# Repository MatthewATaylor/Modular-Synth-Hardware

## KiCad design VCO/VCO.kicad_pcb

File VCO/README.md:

# VCO

A simple voltage controlled oscillator based on the [VCO-1 design by Thomas Henry](https://www.birthofasynth.com/Thomas_Henry/Pages/VCO-1.html), including:

* Triangle, sine, PWM, and sawtooth outputs
* Linear and exponential FM
* A switch for choosing between slow (LFO) and fast (1V/oct, audio rate) frequency ranges

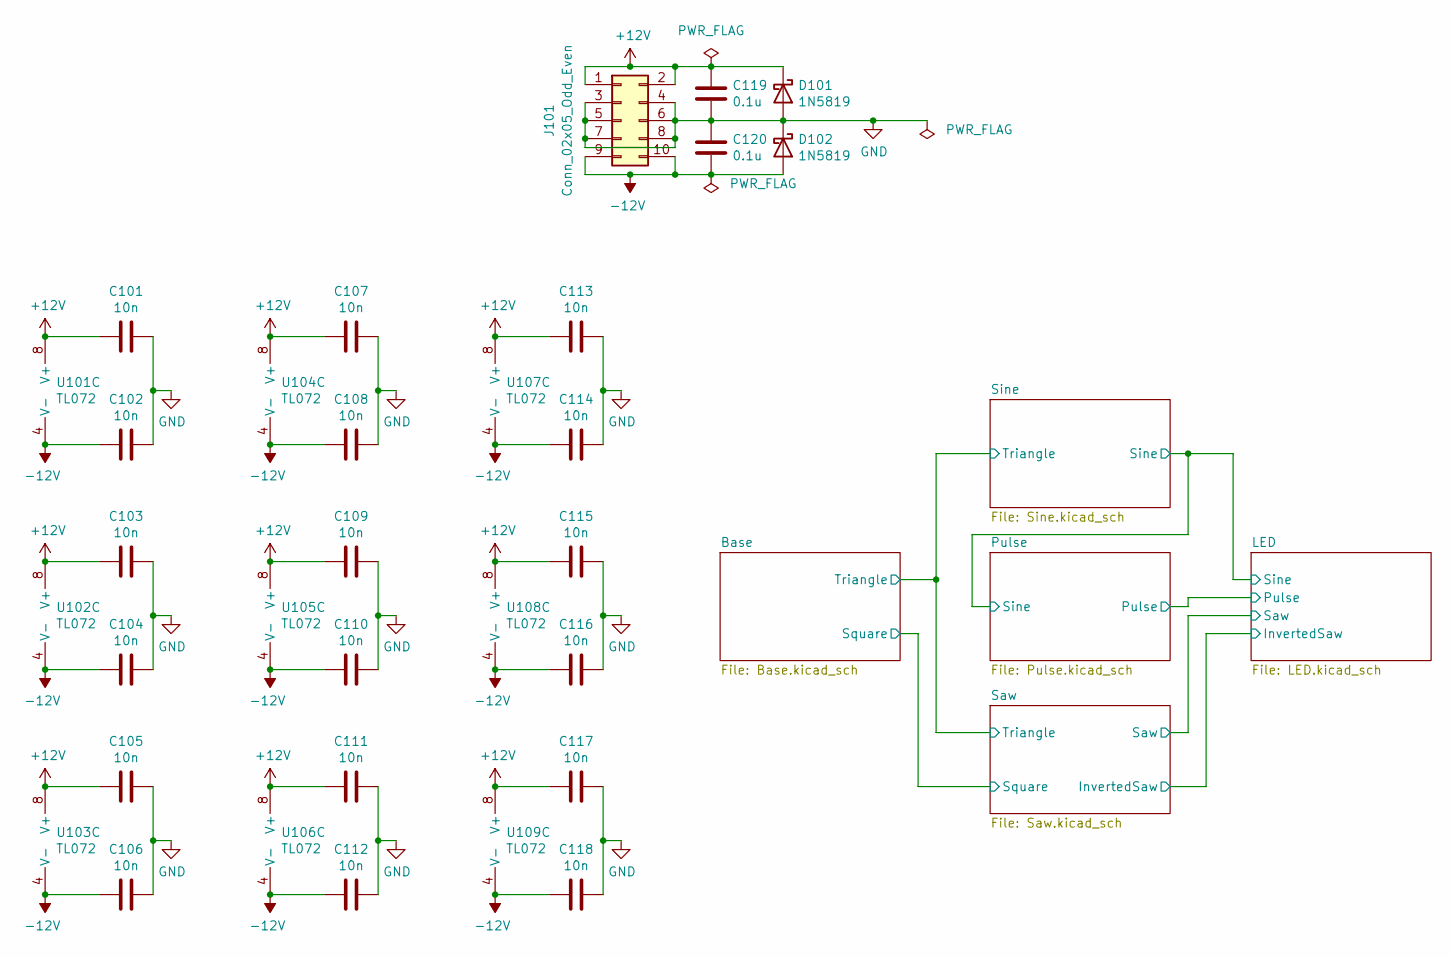
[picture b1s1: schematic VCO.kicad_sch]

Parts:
C101, C102, C103, C104, C105, C106, C107, C108, C109, C110, C111, C112, C113, C114, C115, C116, C117, C118: 10n; C_Disc_D5.0mm_W2.5mm_P5.00mm
C119, C120: 0.1u; C_Disc_D5.0mm_W2.5mm_P5.00mm
D101, D102: 1N5819; D_DO-41_SOD81_P10.16mm_Horizontal
J101: Conn_02x05_Odd_Even; PinHeader_2x05_P2.54mm_Vertical
U101, U102, U103, U104, U105, U106, U107, U108, U109: TL072; DIP-8_W7.62mm_Socket

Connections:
+12V: C101.1, C103.1, C105.1, C107.1, C109.1, C111.1, C113.1, C115.1, C117.1, C119.1, D101.1 (K), J101.1, J101.2, U101.8 (V+), U102.8 (V+), U103.8 (V+), U104.8 (V+), U105.8 (V+), U106.8 (V+), U107.8 (V+), U108.8 (V+), U109.8 (V+); also elsewhere on the board
-12V: C102.1, C104.1, C106.1, C108.1, C110.1, C112.1, C114.1, C116.1, C118.1, C120.2, D102.2 (A), J101.9, J101.10, U101.4 (V-), U102.4 (V-), U103.4 (V-), U104.4 (V-), U105.4 (V-), U106.4 (V-), U107.4 (V-), U108.4 (V-), U109.4 (V-); also elsewhere on the board
GND: C101.2, C102.2, C103.2, C104.2, C105.2, C106.2, C107.2, C108.2, C109.2, C110.2, C111.2, C112.2, C113.2, C114.2, C115.2, C116.2, C117.2, C118.2, C119.2, C120.1, D101.2 (A), D102.1 (K), J101.3, J101.4, J101.5, J101.6, J101.7, J101.8; also elsewhere on the board

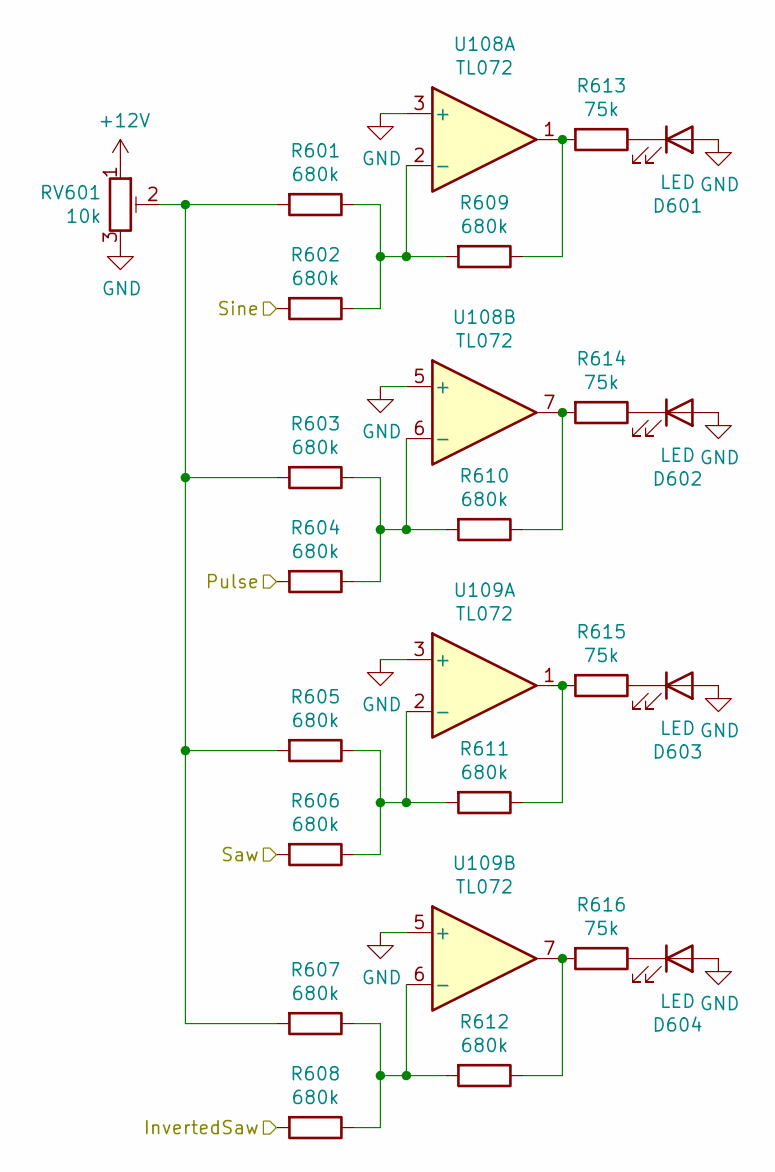
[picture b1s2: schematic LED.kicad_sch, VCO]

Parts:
D601, D602, D603, D604: LED; LED_D5.0mm
R601, R602, R603, R604, R605, R606, R607, R608, R609, R610, R611, R612: 680k; R_Axial_DIN0207_L6.3mm_D2.5mm_P7.62mm_Horizontal
R613, R614, R615, R616: 75k; R_Axial_DIN0207_L6.3mm_D2.5mm_P7.62mm_Horizontal
RV601: 10k; Potentiometer_Runtron_RM-065_Vertical_Improved
U108, U109: TL072; DIP-8_W7.62mm_Socket

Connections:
+12V: RV601.1; also elsewhere on the board
/LED/InvertedSaw: R608.2; also elsewhere on the board
/LED/Pulse: R604.2; also elsewhere on the board
/LED/Saw: R606.2; also elsewhere on the board
/LED/Sine: R602.2; also elsewhere on the board
GND: D601.2 (A), D602.2 (A), D603.2 (A), D604.2 (A), RV601.3, U108.3 (+), U108.5 (+), U109.3 (+), U109.5 (+); also elsewhere on the board
unnamed: D601.1 (K), R613.1
unnamed: D602.1 (K), R614.1
unnamed: D603.1 (K), R615.1
unnamed: D604.1 (K), R616.1
unnamed: R601.1, R602.1, R609.2, U108.2 (-)
unnamed: R601.2, R603.2, R605.2, R607.2, RV601.2
unnamed: R603.1, R604.1, R610.2, U108.6 (-)
unnamed: R605.1, R606.1, R611.2, U109.2 (-)
unnamed: R607.1, R608.1, R612.2, U109.6 (-)
unnamed: R609.1, R613.2, U108.1
unnamed: R610.1, R614.2, U108.7
unnamed: R611.1, R615.2, U109.1
unnamed: R612.1, R616.2, U109.7

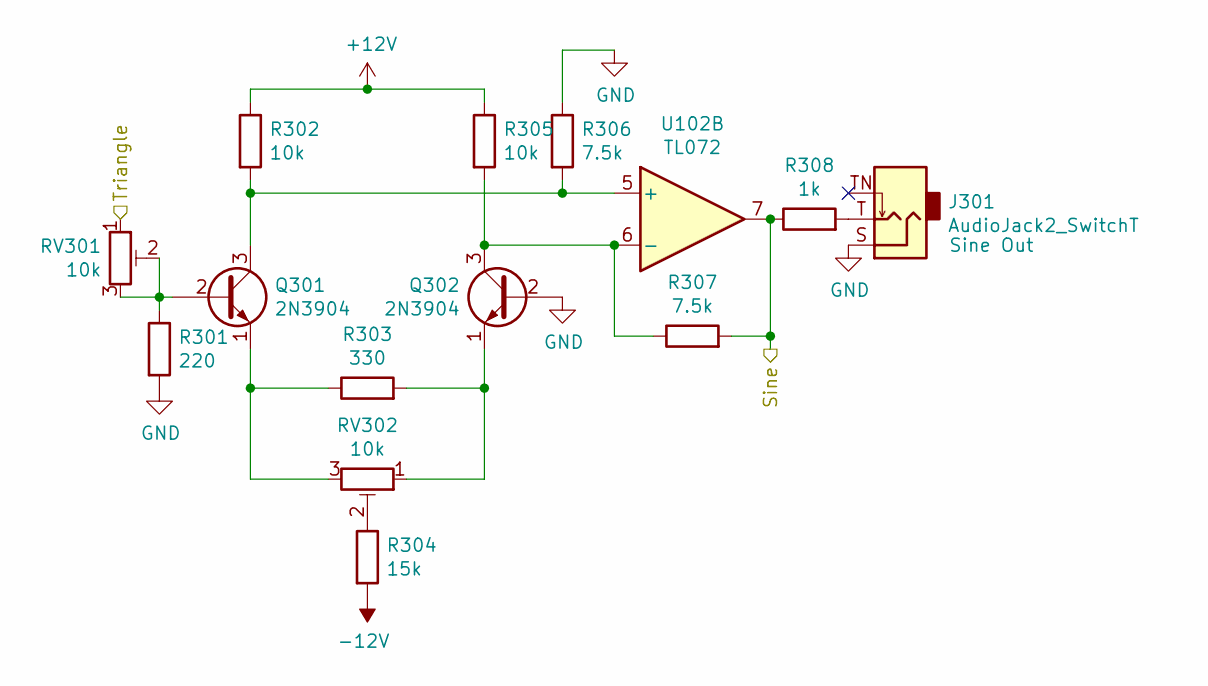
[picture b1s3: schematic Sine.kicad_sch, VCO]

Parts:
J301: AudioJack2_SwitchT; Jack_3.5mm_QingPu_WQP-PJ398SM_Vertical_CircularHoles
Q301, Q302: 2N3904; TO-92_Inline
R301: 220; R_Axial_DIN0207_L6.3mm_D2.5mm_P7.62mm_Horizontal
R302, R305: 10k; R_Axial_DIN0207_L6.3mm_D2.5mm_P7.62mm_Horizontal
R303: 330; R_Axial_DIN0207_L6.3mm_D2.5mm_P7.62mm_Horizontal
R304: 15k; R_Axial_DIN0207_L6.3mm_D2.5mm_P7.62mm_Horizontal
R306, R307: 7.5k; R_Axial_DIN0207_L6.3mm_D2.5mm_P7.62mm_Horizontal
R308: 1k; R_Axial_DIN0207_L6.3mm_D2.5mm_P7.62mm_Horizontal
RV301, RV302: 10k; Potentiometer_Runtron_RM-065_Vertical_Improved
U102: TL072; DIP-8_W7.62mm_Socket

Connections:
+12V: R302.1, R305.1; also elsewhere on the board
-12V: R304.2; also elsewhere on the board
/Base/Triangle: RV301.1; also elsewhere on the board
/LED/Sine: R307.2, R308.1, U102.7; also elsewhere on the board
GND: J301.S, Q302.2 (B), R301.2, R306.1; also elsewhere on the board
unnamed: J301.T, R308.2
unnamed: Q301.1 (E), R303.1, RV302.3
unnamed: Q301.2 (B), R301.1, RV301.2, RV301.3
unnamed: Q301.3 (C), R302.2, R306.2, U102.5 (+)
unnamed: Q302.1 (E), R303.2, RV302.1
unnamed: Q302.3 (C), R305.2, R307.1, U102.6 (-)
unnamed: R304.1, RV302.2

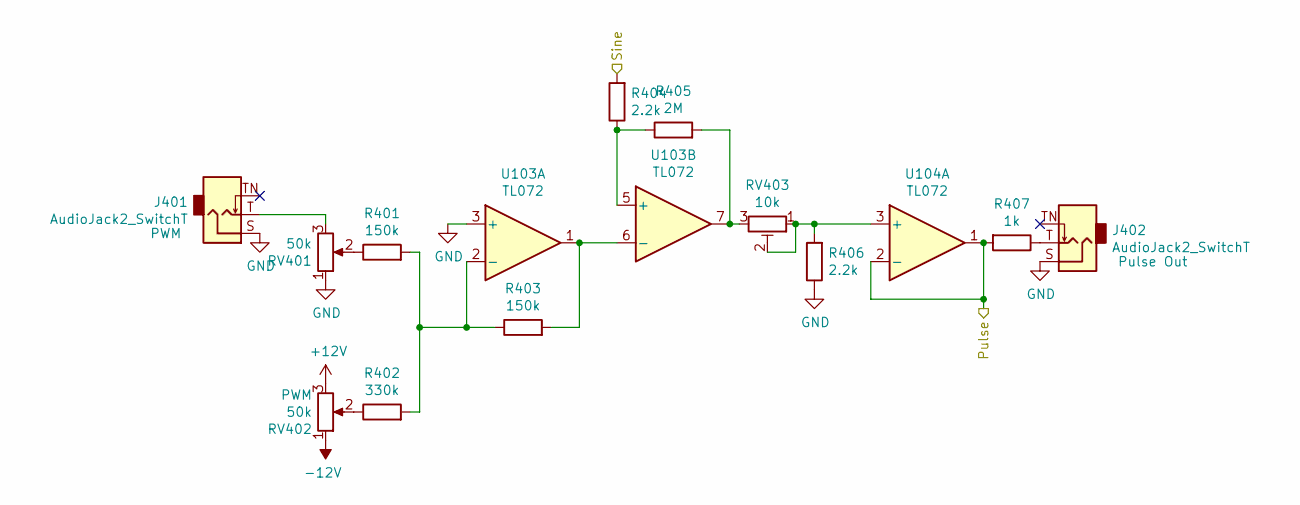
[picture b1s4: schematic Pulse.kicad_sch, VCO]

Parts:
J401, J402: AudioJack2_SwitchT; Jack_3.5mm_QingPu_WQP-PJ398SM_Vertical_CircularHoles
R401, R403: 150k; R_Axial_DIN0207_L6.3mm_D2.5mm_P7.62mm_Horizontal
R402: 330k; R_Axial_DIN0207_L6.3mm_D2.5mm_P7.62mm_Horizontal
R404, R406: 2.2k; R_Axial_DIN0207_L6.3mm_D2.5mm_P7.62mm_Horizontal
R405: 2M; R_Axial_DIN0207_L6.3mm_D2.5mm_P7.62mm_Horizontal
R407: 1k; R_Axial_DIN0207_L6.3mm_D2.5mm_P7.62mm_Horizontal
RV401, RV402: 50k; Potentiometer_Alpha_RD901F-40-00D_Single_Vertical_CircularH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
RV403: 10k; Potentiometer_Runtron_RM-065_Vertical_Improved
U103, U104: TL072; DIP-8_W7.62mm_Socket

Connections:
+12V: RV402.3; also elsewhere on the board
-12V: RV402.1; also elsewhere on the board
/LED/Pulse: R407.2, U104.1, U104.2 (-); also elsewhere on the board
/LED/Sine: R404.2; also elsewhere on the board
GND: J401.S, J402.S, R406.1, RV401.1, U103.3 (+); also elsewhere on the board
unnamed: J401.T, RV401.3
unnamed: J402.T, R407.1
unnamed: R401.1, RV401.2
unnamed: R401.2, R402.2, R403.1, U103.2 (-)
unnamed: R402.1, RV402.2
unnamed: R403.2, U103.1, U103.6 (-)
unnamed: R404.1, R405.1, U103.5 (+)
unnamed: R405.2, RV403.3, U103.7
unnamed: R406.2, RV403.1, RV403.2, U104.3 (+)

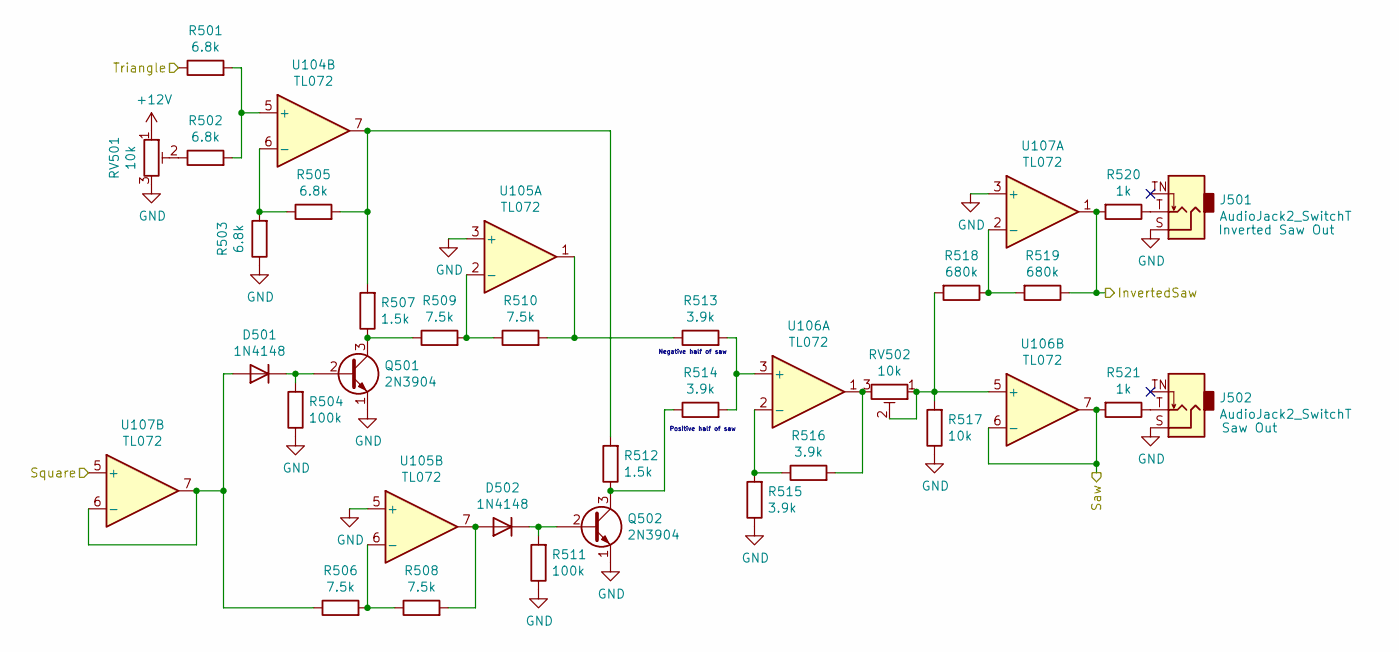
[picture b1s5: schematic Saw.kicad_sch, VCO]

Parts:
D501, D502: 1N4148; D_DO-35_SOD27_P7.62mm_Horizontal
J501, J502: AudioJack2_SwitchT; Jack_3.5mm_QingPu_WQP-PJ398SM_Vertical_CircularHoles
Q501, Q502: 2N3904; TO-92_Inline
R501, R502, R503, R505: 6.8k; R_Axial_DIN0207_L6.3mm_D2.5mm_P7.62mm_Horizontal
R504, R511: 100k; R_Axial_DIN0207_L6.3mm_D2.5mm_P7.62mm_Horizontal
R506, R508, R509, R510: 7.5k; R_Axial_DIN0207_L6.3mm_D2.5mm_P7.62mm_Horizontal
R507, R512: 1.5k; R_Axial_DIN0207_L6.3mm_D2.5mm_P7.62mm_Horizontal
R513, R514, R515, R516: 3.9k; R_Axial_DIN0207_L6.3mm_D2.5mm_P7.62mm_Horizontal
R517: 10k; R_Axial_DIN0207_L6.3mm_D2.5mm_P7.62mm_Horizontal
R518, R519: 680k; R_Axial_DIN0207_L6.3mm_D2.5mm_P7.62mm_Horizontal
R520, R521: 1k; R_Axial_DIN0207_L6.3mm_D2.5mm_P7.62mm_Horizontal
RV501, RV502: 10k; Potentiometer_Runtron_RM-065_Vertical_Improved
U104, U105, U106, U107: TL072; DIP-8_W7.62mm_Socket

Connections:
+12V: RV501.1; also elsewhere on the board
/Base/Square: U107.5 (+); also elsewhere on the board
/Base/Triangle: R501.1; also elsewhere on the board
/LED/InvertedSaw: R519.1, R520.2, U107.1; also elsewhere on the board
/LED/Saw: R521.2, U106.6 (-), U106.7; also elsewhere on the board
GND: J501.S, J502.S, Q501.1 (E), Q502.1 (E), R503.1, R504.1, R511.1, R515.1, R517.1, RV501.3, U105.3 (+), U105.5 (+), U107.3 (+); also elsewhere on the board
unnamed: D501.1 (K), Q501.2 (B), R504.2
unnamed: D501.2 (A), R506.1, U107.6 (-), U107.7
unnamed: D502.1 (K), Q502.2 (B), R511.2
unnamed: D502.2 (A), R508.2, U105.7
unnamed: J501.T, R520.1
unnamed: J502.T, R521.1
unnamed: Q501.3 (C), R507.1, R509.1
unnamed: Q502.3 (C), R512.1, R514.1
unnamed: R501.2, R502.2, U104.5 (+)
unnamed: R502.1, RV501.2
unnamed: R503.2, R505.1, U104.6 (-)
unnamed: R505.2, R507.2, R512.2, U104.7
unnamed: R506.2, R508.1, U105.6 (-)
unnamed: R509.2, R510.1, U105.2 (-)
unnamed: R510.2, R513.1, U105.1
unnamed: R513.2, R514.2, U106.3 (+)
unnamed: R515.2, R516.1, U106.2 (-)
unnamed: R516.2, RV502.3, U106.1
unnamed: R517.2, R518.2, RV502.1, RV502.2, U106.5 (+)
unnamed: R518.1, R519.2, U107.2 (-)

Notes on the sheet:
Positive half of saw
Negative half of saw

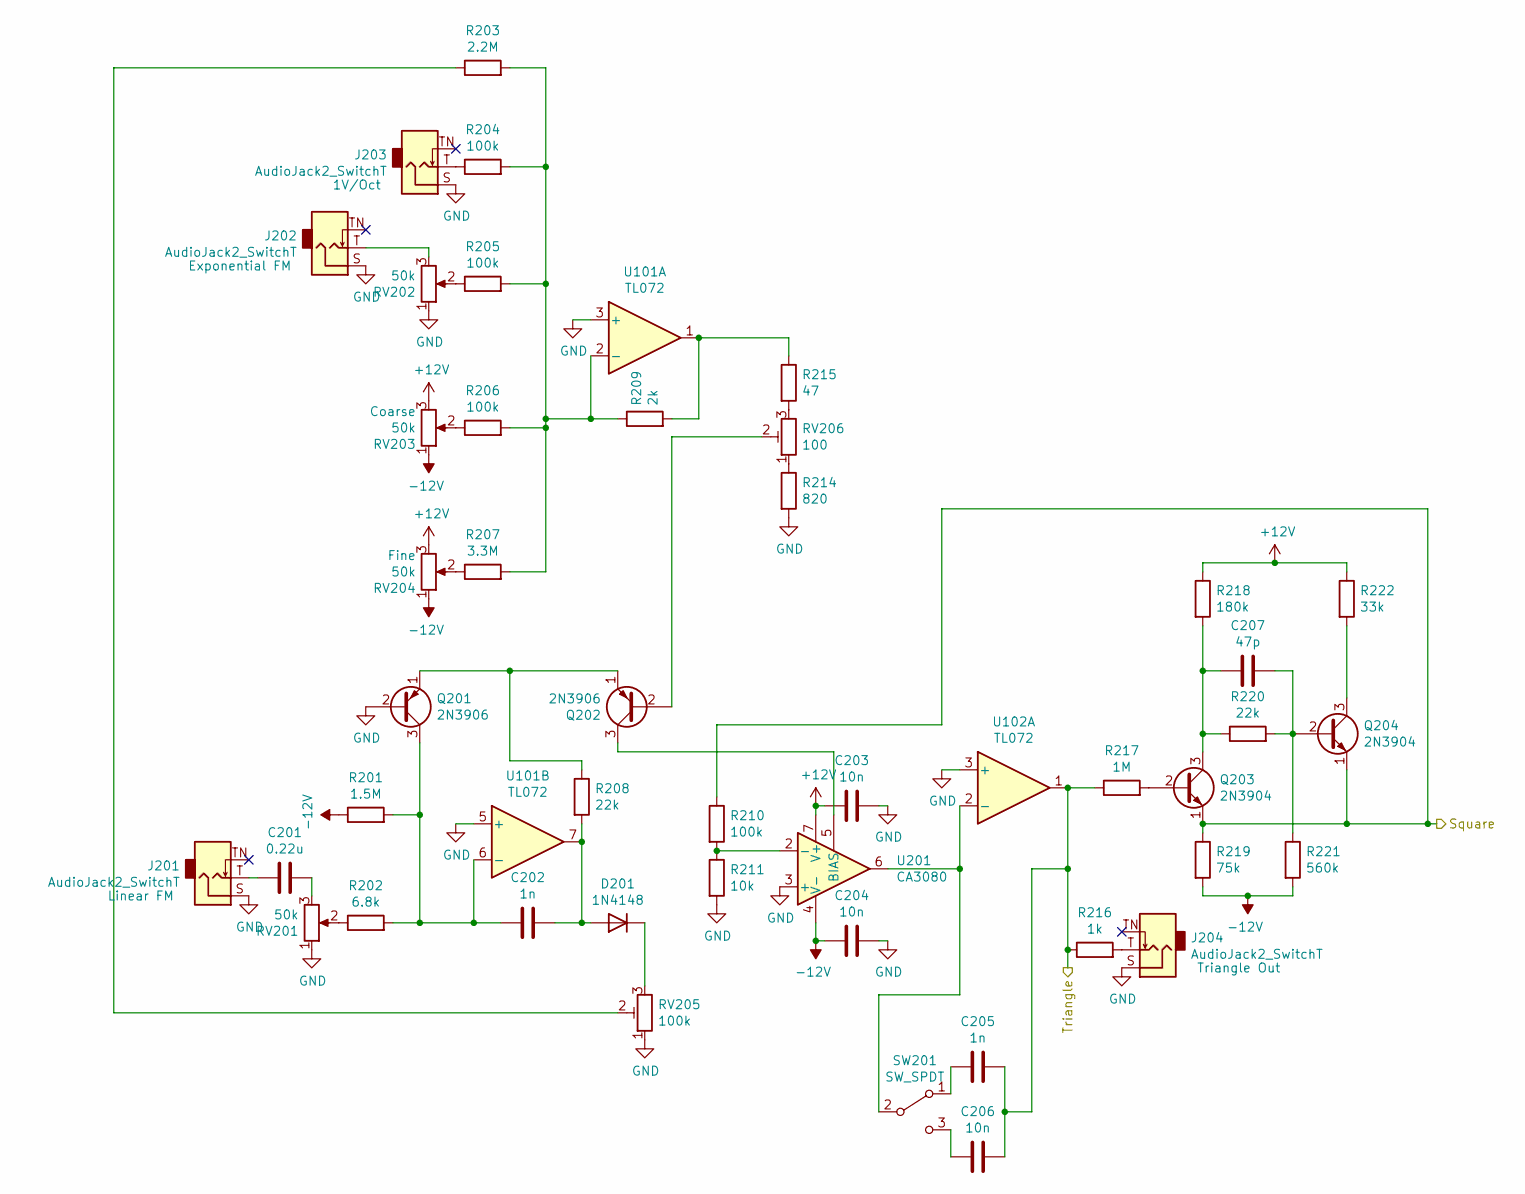
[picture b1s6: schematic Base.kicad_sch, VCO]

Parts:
C201: 0.22u; C_Disc_D5.0mm_W2.5mm_P5.00mm
C202, C205: 1n; C_Disc_D5.0mm_W2.5mm_P5.00mm
C203, C204, C206: 10n; C_Disc_D5.0mm_W2.5mm_P5.00mm
C207: 47p; C_Disc_D5.0mm_W2.5mm_P5.00mm
D201: 1N4148; D_DO-35_SOD27_P7.62mm_Horizontal
J201, J202, J203, J204: AudioJack2_SwitchT; Jack_3.5mm_QingPu_WQP-PJ398SM_Vertical_CircularHoles
Q201, Q202: 2N3906; TO-92_Inline
Q203, Q204: 2N3904; TO-92_Inline
R201: 1.5M; R_Axial_DIN0207_L6.3mm_D2.5mm_P7.62mm_Horizontal
R202: 6.8k; R_Axial_DIN0207_L6.3mm_D2.5mm_P7.62mm_Horizontal
R203: 2.2M; R_Axial_DIN0207_L6.3mm_D2.5mm_P7.62mm_Horizontal
R204, R205, R206, R210: 100k; R_Axial_DIN0207_L6.3mm_D2.5mm_P7.62mm_Horizontal
R207: 3.3M; R_Axial_DIN0207_L6.3mm_D2.5mm_P7.62mm_Horizontal
R208, R220: 22k; R_Axial_DIN0207_L6.3mm_D2.5mm_P7.62mm_Horizontal
R209: 2k; R_Axial_DIN0207_L6.3mm_D2.5mm_P7.62mm_Horizontal
R211: 10k; R_Axial_DIN0207_L6.3mm_D2.5mm_P7.62mm_Horizontal
R214: 820; R_Axial_DIN0207_L6.3mm_D2.5mm_P7.62mm_Horizontal
R215: 47; R_Axial_DIN0207_L6.3mm_D2.5mm_P7.62mm_Horizontal
R216: 1k; R_Axial_DIN0207_L6.3mm_D2.5mm_P7.62mm_Horizontal
R217: 1M; R_Axial_DIN0207_L6.3mm_D2.5mm_P7.62mm_Horizontal
R218: 180k; R_Axial_DIN0207_L6.3mm_D2.5mm_P7.62mm_Horizontal
R219: 75k; R_Axial_DIN0207_L6.3mm_D2.5mm_P7.62mm_Horizontal
R221: 560k; R_Axial_DIN0207_L6.3mm_D2.5mm_P7.62mm_Horizontal
R222: 33k; R_Axial_DIN0207_L6.3mm_D2.5mm_P7.62mm_Horizontal
RV201, RV202, RV203, RV204: 50k; Potentiometer_Alpha_RD901F-40-00D_Single_Vertical_CircularH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
RV205: 100k; Potentiometer_Bourns_3296W_Vertical
RV206: 100; Potentiometer_Bourns_3296W_Vertical
SW201: SW_SPDT; MTS-102_MTS-103_MTS-112_MTS-113_MTS-123
U101, U102: TL072; DIP-8_W7.62mm_Socket
U201: CA3080; DIP-8_W7.62mm_Socket

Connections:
+12V: C203.1, R218.1, R222.1, RV203.3, RV204.3, U201.7 (V+); also elsewhere on the board
-12V: C204.1, R201.1, R219.2, R221.2, RV203.1, RV204.1, U201.4 (V-); also elsewhere on the board
/Base/Square: Q203.1 (E), Q204.1 (E), R210.1, R219.1; also elsewhere on the board
/Base/Triangle: C205.2, C206.2, R216.1, R217.1, U102.1; also elsewhere on the board
GND: C203.2, C204.2, J201.S, J202.S, J203.S, J204.S, Q201.2 (B), R211.2, R214.2, RV201.1, RV202.1, RV205.1, U101.3 (+), U101.5 (+), U102.3 (+), U201.3 (+); also elsewhere on the board
unnamed: C201.1, J201.T
unnamed: C201.2, RV201.3
unnamed: C202.1, Q201.3 (C), R201.2, R202.2, U101.6 (-)
unnamed: C202.2, D201.2 (A), R208.2, U101.7
unnamed: C205.1, SW201.1 (A)
unnamed: C206.1, SW201.3 (C)
unnamed: C207.1, Q203.3 (C), R218.2, R220.1
unnamed: C207.2, Q204.2 (B), R220.2, R221.1
unnamed: D201.1 (K), RV205.3
unnamed: J202.T, RV202.3
unnamed: J203.T, R204.1
unnamed: J204.T, R216.2
unnamed: Q201.1 (E), Q202.1 (E), R208.1
unnamed: Q202.2 (B), RV206.2
unnamed: Q202.3 (C), U201.5 (BIAS)
unnamed: Q203.2 (B), R217.2
unnamed: Q204.3 (C), R222.2
unnamed: R202.1, RV201.2
unnamed: R203.1, RV205.2
unnamed: R203.2, R204.2, R205.2, R206.2, R207.2, R209.1, U101.2 (-)
unnamed: R205.1, RV202.2
unnamed: R206.1, RV203.2
unnamed: R207.1, RV204.2
unnamed: R209.2, R215.1, U101.1
unnamed: R210.2, R211.1, U201.2 (-)
unnamed: R214.1, RV206.1
unnamed: R215.2, RV206.3
unnamed: SW201.2 (B), U102.2 (-), U201.6

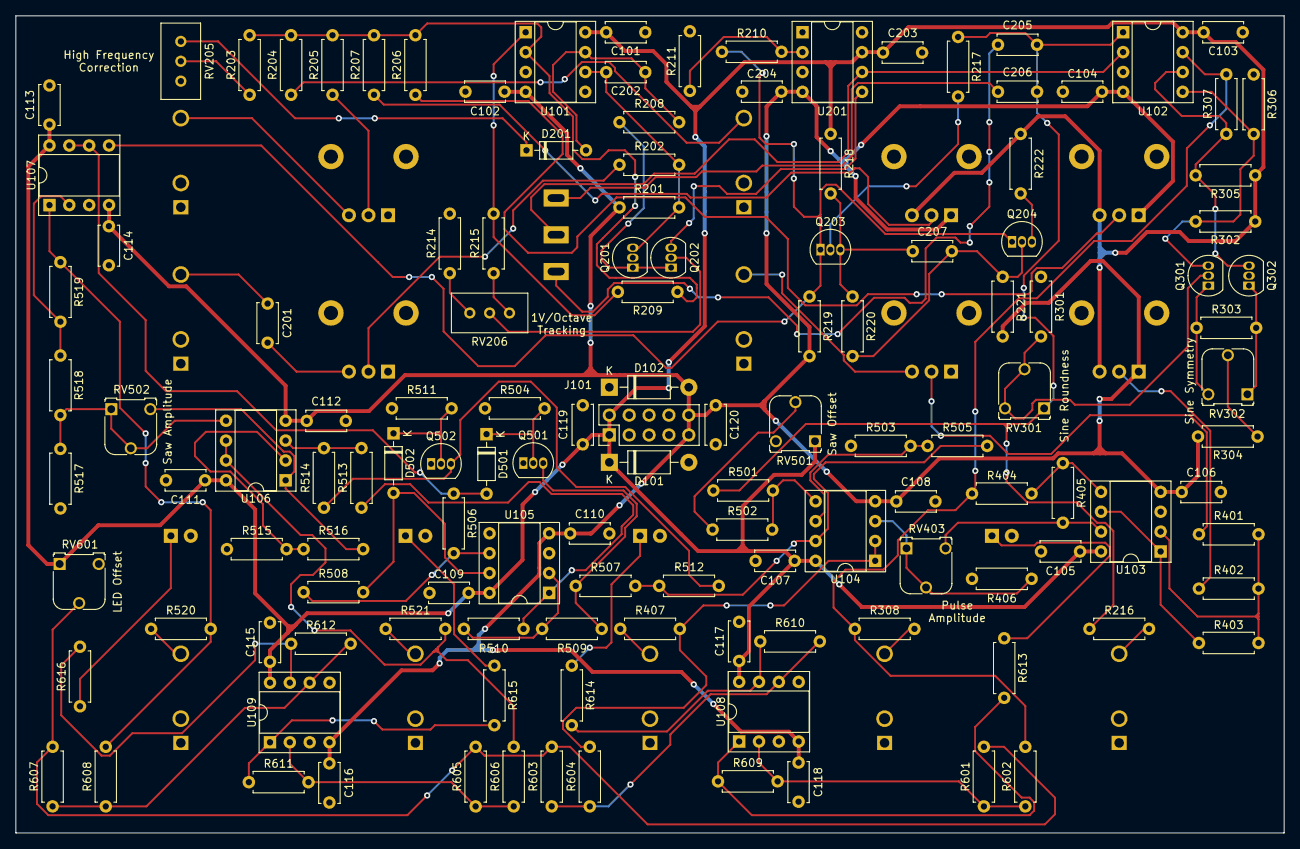
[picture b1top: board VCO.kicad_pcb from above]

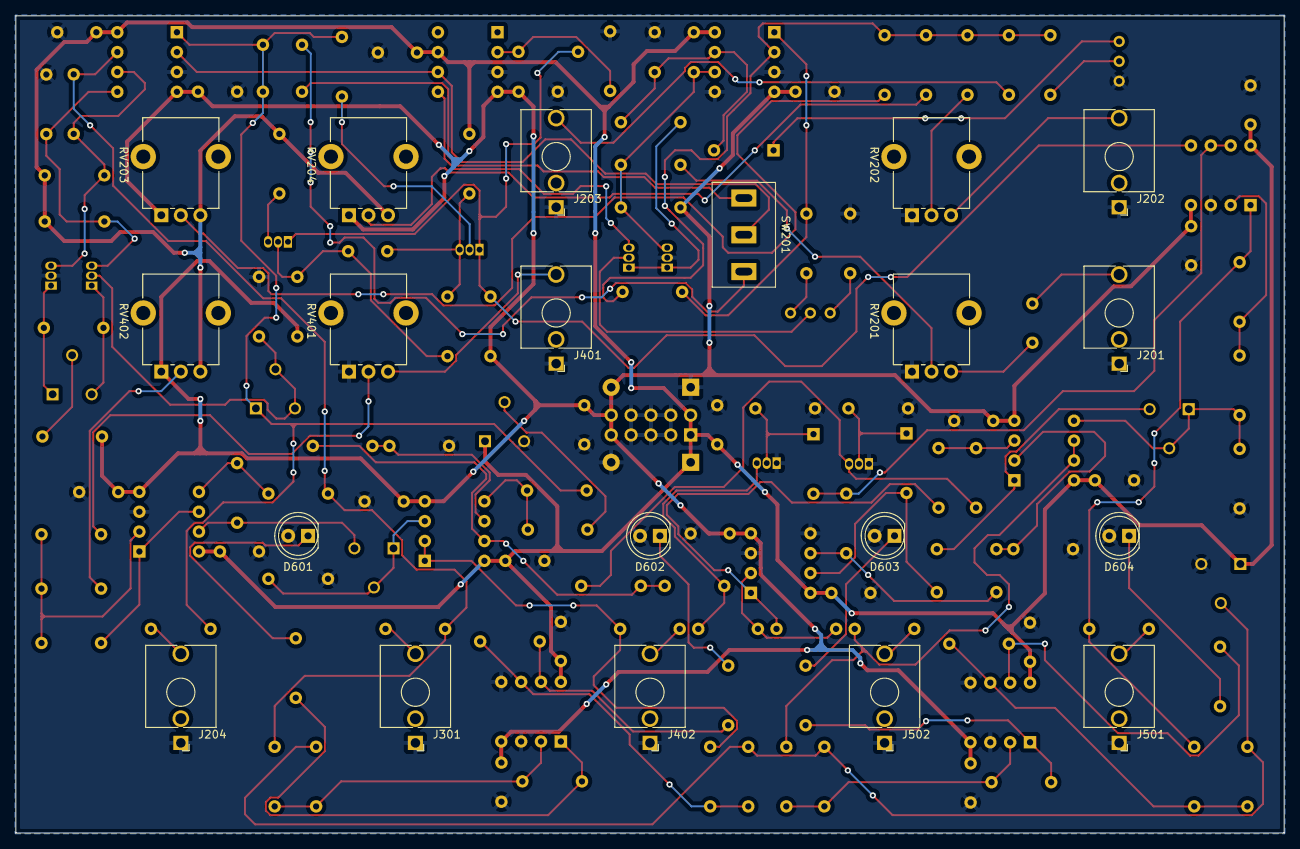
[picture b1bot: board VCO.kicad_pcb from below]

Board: 2 copper layers, 162.2 x 104.5 mm, 151 parts (20 on the bottom side), 86 nets.

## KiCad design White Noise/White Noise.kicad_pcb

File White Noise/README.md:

# White Noise

A white noise generator based on [René Schmitz's design](https://www.schmitzbits.de/noise.html).

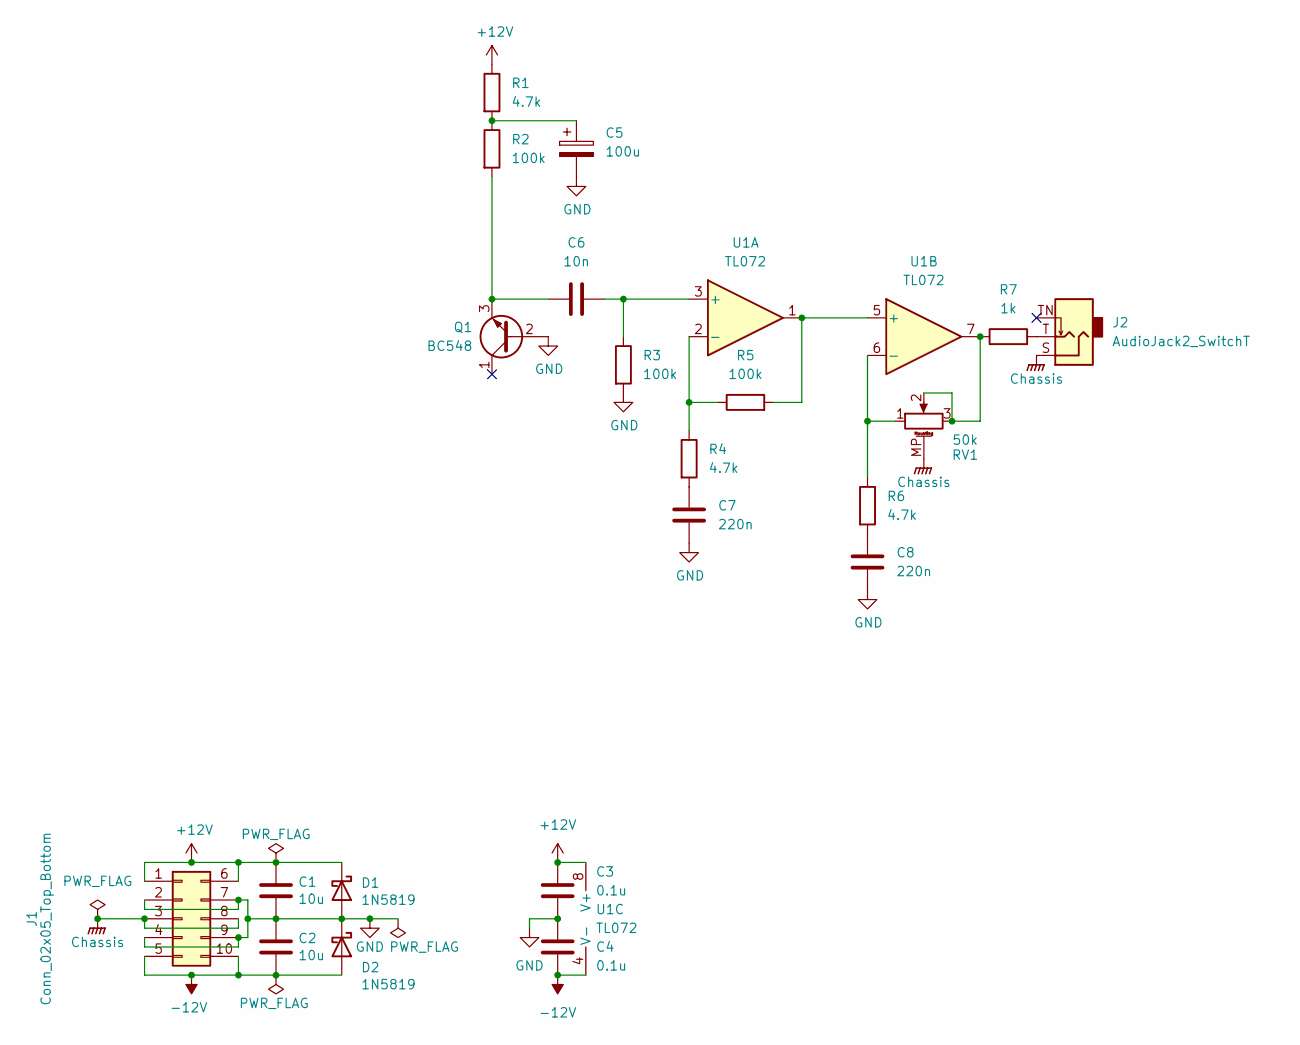
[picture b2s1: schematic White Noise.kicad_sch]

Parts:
C1, C2: 10u; C_Disc_D5.5mm_W4.0mm_P2.50mm
C3, C4: 0.1u; C_Disc_D5.5mm_W2.5mm_P2.50mm
C5: 100u; CP_Radial_D5.0mm_P2.00mm
C6: 10n; C_Disc_D5.5mm_W2.5mm_P2.50mm
C7, C8: 220n; C_Disc_D5.5mm_W2.5mm_P2.50mm
D1, D2: 1N5819; D_DO-41_SOD81_P10.16mm_Horizontal
J1: Conn_02x05_Top_Bottom; Molex_Mini-Fit_Jr_5566-10A_2x05_P4.20mm_Vertical
J2: AudioJack2_SwitchT; Jack_3.5mm_QingPu_WQP-PJ398SM_Vertical_CircularHoles
Q1: BC548; TO-92_HandSolder
R1, R4, R6: 4.7k; R_Axial_DIN0207_L6.3mm_D2.5mm_P7.62mm_Horizontal
R2, R3, R5: 100k; R_Axial_DIN0207_L6.3mm_D2.5mm_P7.62mm_Horizontal
R7: 1k; R_Axial_DIN0207_L6.3mm_D2.5mm_P7.62mm_Horizontal
RV1: 50k; Potentiometer_Alpha_RD901F-40-00D_Single_Vertical_MP
U1: TL072; DIP-8_W7.62mm_Socket

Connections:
+12V: C1.1, C3.2, D1.1 (K), J1.1, J1.6, R1.1, U1.8 (V+)
-12V: C2.2, C4.1, D2.2 (A), J1.5, J1.10, U1.4 (V-)
Chassis: J1.3, J1.8, J2.S, RV1.MP (MountPin)
GND: C1.2, C2.1, C3.1, C4.2, C5.2, C7.1, C8.1, D1.2 (A), D2.1 (K), J1.2, J1.4, J1.7, J1.9, Q1.2 (B), R3.2
unnamed: C5.1, R1.2, R2.1
unnamed: C7.2, R4.2
unnamed: C8.2, R6.2
unnamed: J2.T, R7.2
unnamed: C6.1, Q1.3 (E), R2.2
unnamed: R7.1, RV1.2, RV1.3, U1.7
unnamed: C6.2, R3.1, U1.3 (+)
unnamed: R4.1, R5.1, U1.2 (-)
unnamed: R5.2, U1.1, U1.5 (+)
unnamed: R6.1, RV1.1, U1.6 (-)

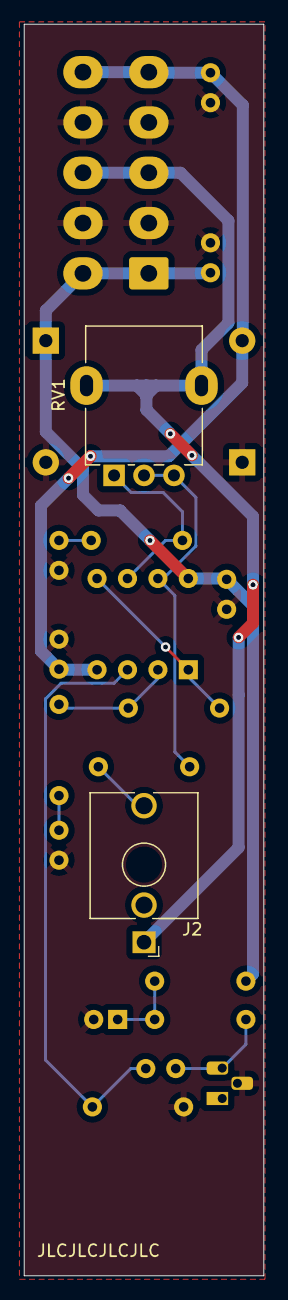
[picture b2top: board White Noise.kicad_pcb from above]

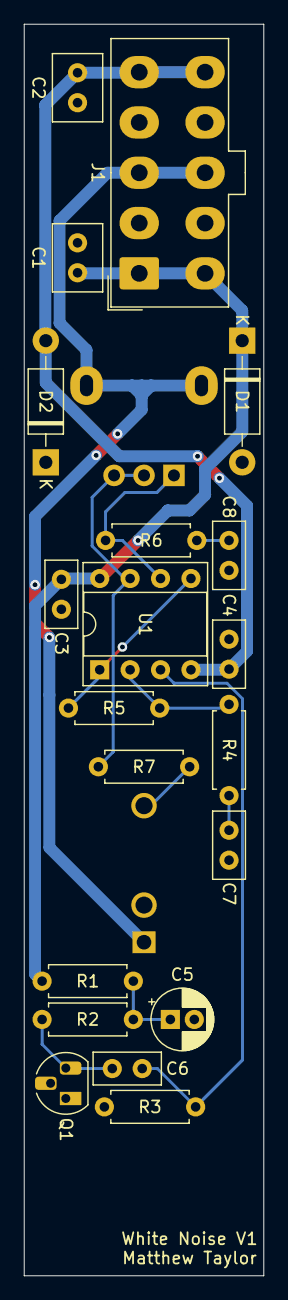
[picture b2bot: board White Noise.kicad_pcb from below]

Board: 2 copper layers, 20.0 x 104.5 mm, 22 parts (20 on the bottom side), 14 nets.
